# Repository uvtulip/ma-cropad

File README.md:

# ma-cropad
My first macropad ever. I plan to create a 1x5 macropad with 1 rotary encoder and use KMK library for writing firmware.

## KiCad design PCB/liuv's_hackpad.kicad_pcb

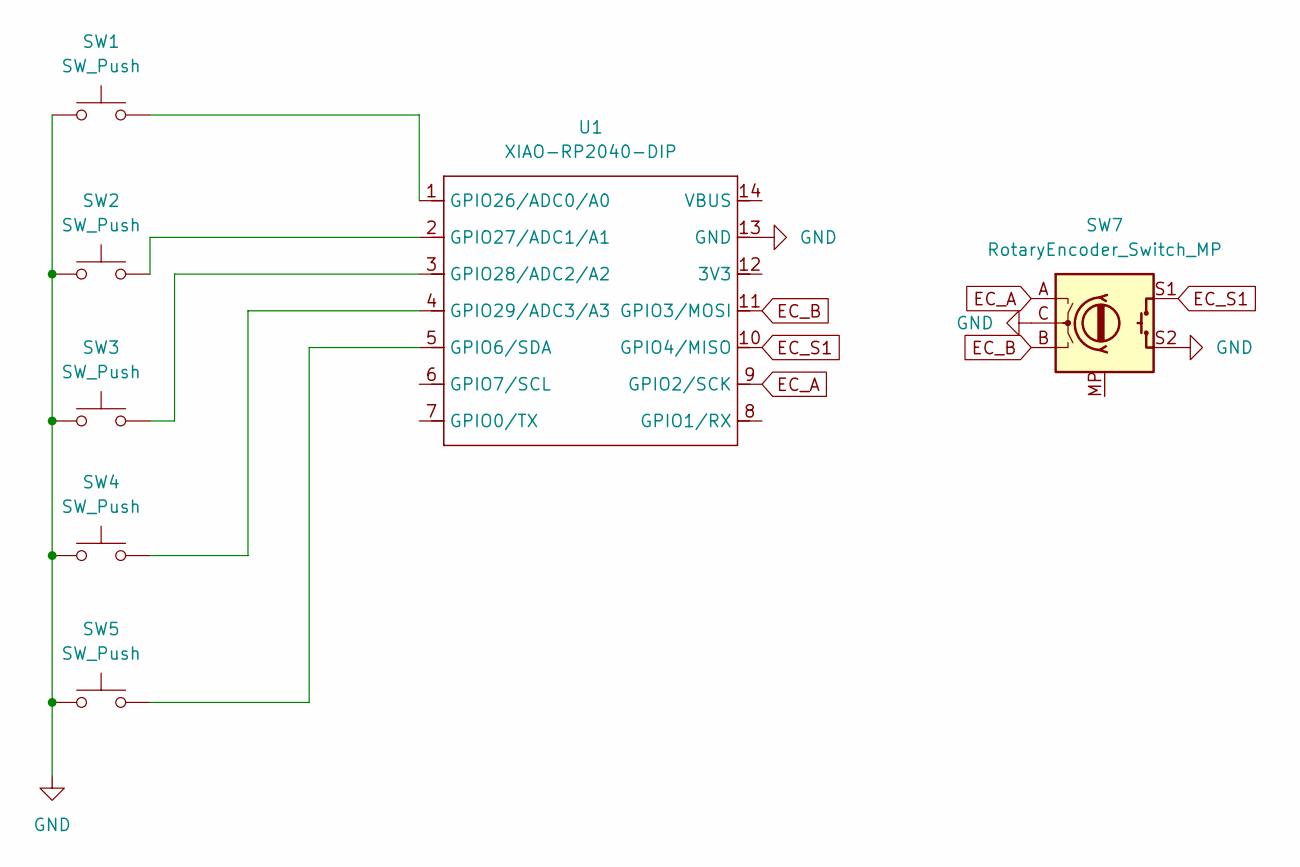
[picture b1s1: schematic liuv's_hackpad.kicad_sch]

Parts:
SW1, SW2, SW3, SW4, SW5: SW_Push; SW_Cherry_MX_1.00u_PCB
SW7: RotaryEncoder_Switch_MP; RotaryEncoder_Alps_EC11E-Switch_Vertical_H20mm
U1: XIAO-RP2040-DIP

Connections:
EC_A: SW7.A, U1.9 (GPIO2/SCK)
EC_B: SW7.B, U1.11 (GPIO3/MOSI)
EC_S1: SW7.S1, U1.10 (GPIO4/MISO)
GND: SW1.1, SW2.1, SW3.1, SW4.1, SW5.1, SW7.C, SW7.S2, U1.13 (GND)
unnamed: SW5.2, U1.5 (GPIO6/SDA)
unnamed: SW1.2, U1.1 (GPIO26/ADC0/A0)
unnamed: SW2.2, U1.2 (GPIO27/ADC1/A1)
unnamed: SW3.2, U1.3 (GPIO28/ADC2/A2)
unnamed: SW4.2, U1.4 (GPIO29/ADC3/A3)

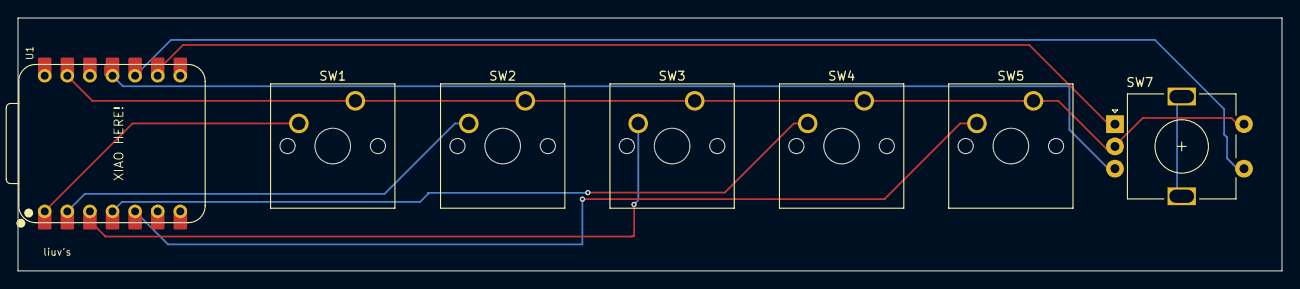
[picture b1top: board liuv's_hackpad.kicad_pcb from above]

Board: 2 copper layers, 142.1 x 28.4 mm, 7 parts (0 on the bottom side), 9 nets.

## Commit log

2025-12-30 upload images for readme
2025-12-30 Fix image paths in README.md
    Updated image paths to reflect new directory structure.
